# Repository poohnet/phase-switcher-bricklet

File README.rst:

Phase Switcher Bricklet
=======================

**This Bricklet is currently in development.**

This repository contains the firmware source code and the hardware design
files. The documentation generator configs can be found at
https://github.com/Tinkerforge/generators

Repository Content
------------------

software/:
 * examples/: Examples for all supported languages
 * build/: Compiled files
 * src/: Source code of firmware
 * Makefile: Makefile to build project

hardware/:
 * Contains KiCad project files and additionally schematics as PDF

datasheets/:
 * Contains datasheets for sensors and complex ICs that are used

Hardware
--------

The hardware is designed with the open source EDA Suite KiCad
(http://www.kicad.org). Before you are able to open the files,
you have to install the Tinkerforge kicad-libraries
(https://github.com/Tinkerforge/kicad-libraries). You can either clone
them directly in hardware/ or clone them in a separate folder and
symlink them into hardware/
(ln -s kicad_path/kicad-libraries project_path/hardware). After that you
can open the .pro file in hardware/ with KiCad and from there view and
modify the schematics and the PCB layout.

Software
--------

If you want to do your own Brick/Bricklet firmware development we highly
recommend that you use our build environment setup script and read the
tutorial (https://www.tinkerforge.com/en/doc/Tutorials/Tutorial_Build_Environment/Tutorial.html).

To compile the C code we recommend you to install the newest GNU Arm Embedded
Toolchain (https://launchpad.net/gcc-arm-embedded/+download).
You also need to install bricklib2 (https://github.com/Tinkerforge/bricklib2).

You can either clone it directly in software/src/ or clone it in a
separate folder and symlink it into software/src/
(ln -s bricklib_path/bricklib2 project_path/software/src/). Finally make sure to
have CMake installed (http://www.cmake.org/cmake/resources/software.html).

After that you can build the firmware by invoking make in software/.
The firmware (.zbin) can then be found in software/build/ and uploaded
with brickv (click button "Flashing" on start screen).

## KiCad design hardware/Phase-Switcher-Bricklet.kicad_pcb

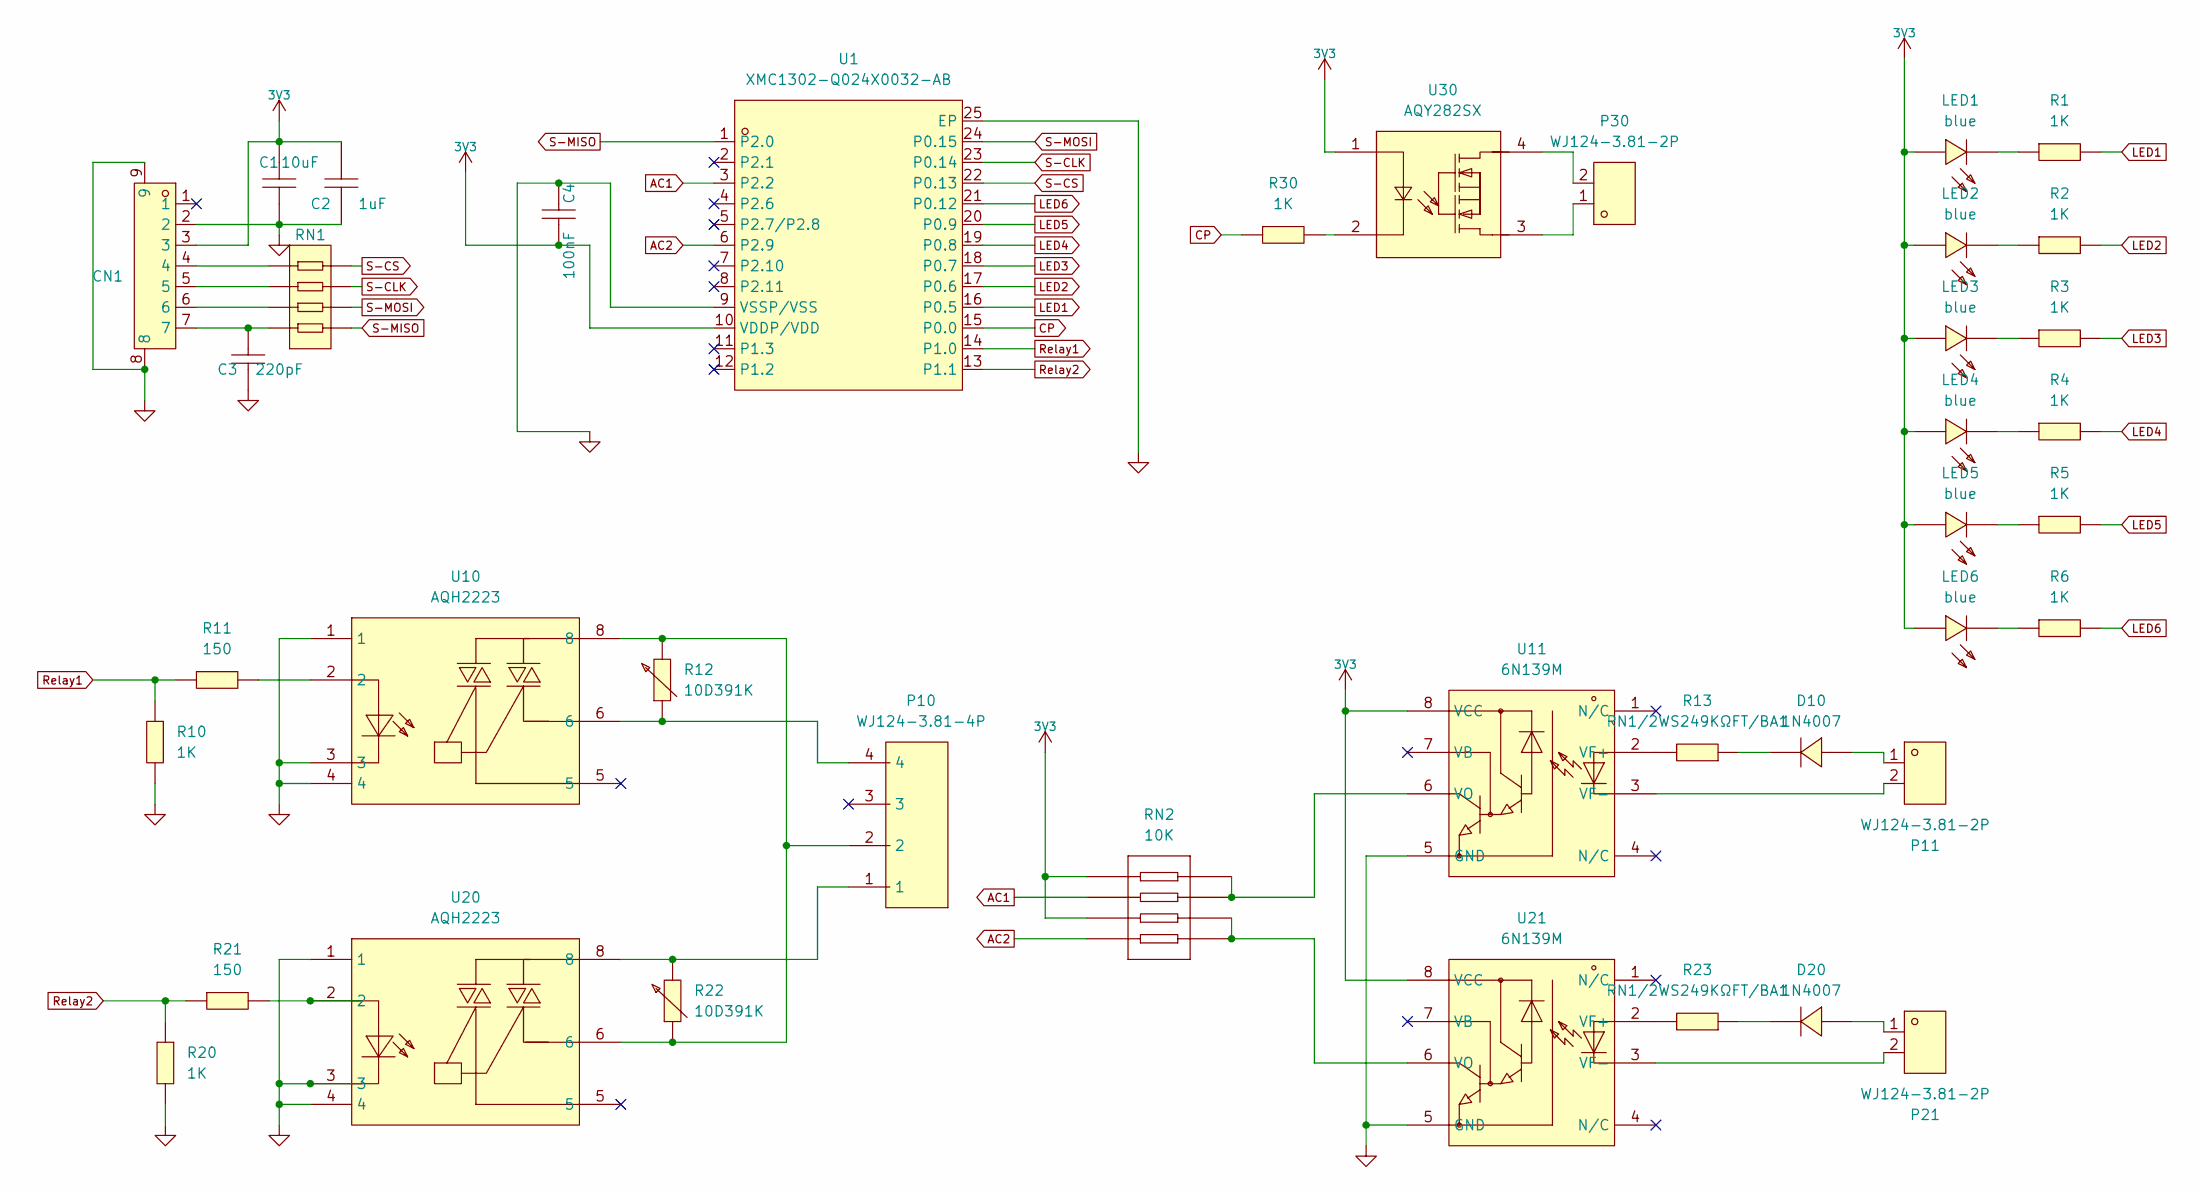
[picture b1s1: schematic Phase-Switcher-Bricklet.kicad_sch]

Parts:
C1: 10uF; C0805; LCSC Part C1222438
C2: 1uF; C0603; LCSC Part C513775
C3: 220pF; C0402; LCSC Part C107025
C4: 100nF; C0603; LCSC Part C30926
CN1: HC-GH-7PWTKK; CONN-SMD_7P-P1.25_HCTL_HC-GH-7PWTKK; LCSC Part C3011949
D10, D20: 1N4007; SOD-123FL_L2.8-W1.8-LS3.7-RD; LCSC Part C2902912
LED1, LED2, LED3, LED4, LED5, LED6: blue; LED0603-RD; LCSC Part C84266
P10: WJ124-3.81-4P; CONN-TH_4P-P3.81_KF124-3.81-4P; LCSC Part C69809
P11, P21, P30: WJ124-3.81-2P; CONN-TH_2P-P3.81_KF124-3.81-2P; LCSC Part C69811
R1, R2, R3, R4, R5, R6, R10, R20, R30: 1K; R0603; LCSC Part C22548
R11, R21: 150; R0603; LCSC Part C114608
R12, R22: 10D391K; RES-TH_L12.5-W6.2-P7.50-D0.9-S6.20; LCSC Part C139984
R13, R23: RN1/2WS249KΩFT/BA1; RES-TH_BD2.2-L6.5-P10.50-D0.6; LCSC Part C385480
RN1: CRA034RJ82RP05; RES-ARRAY-SMD_0603-8P-L3.2-W1.6-BL; LCSC Part C429276
RN2: 10K; RES-ARRAY-SMD_0603-8P-L3.2-W1.6-BL; LCSC Part C396839
U1: XMC1302-Q024X0032-AB; VQFN-24_L4.0-W4.0-P0.50-TL-EP2.7; LCSC Part C5121285
U10, U20: AQH2223; DIP-8_7P-L9.7-W6.4-P2.54-LS7.6-BL-PE7; LCSC Part C128520
U11, U21: 6N139M; DIP-8_L9.4-W6.4-P2.54-LS9.1-BL; LCSC Part C4071
U30: AQY282SX; SOP-4_L4.3-W4.4-P2.54-LS7.0-BL; LCSC Part C250827

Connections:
3V3: C1.1, C2.1, C4.2, CN1.3, LED1.2 (+), LED2.2 (+), LED3.2 (+), LED4.2 (+), LED5.2 (+), LED6.2 (+), RN2.5, RN2.7, U1.10 (VDDP/VDD), U11.8 (VCC), U21.8 (VCC), U30.1
AC1: RN2.6, U1.3 (P2.2)
AC2: RN2.8, U1.6 (P2.9)
CP: R30.1, U1.15 (P0.0)
GND: C1.2, C2.2, C3.2, C4.1, CN1.2, CN1.8, CN1.9, R10.2, R20.2, U1.9 (VSSP/VSS), U1.25 (EP), U10.1, U10.3, U10.4, U11.5 (GND), U20.1, U20.3, U20.4, U21.5 (GND)
LED1: R1.2, U1.16 (P0.5)
LED2: R2.2, U1.17 (P0.6)
LED3: R3.2, U1.18 (P0.7)
LED4: R4.2, U1.19 (P0.8)
LED5: R5.2, U1.20 (P0.9)
LED6: R6.2, U1.21 (P0.12)
unnamed: C3.1, CN1.7, RN1.4
unnamed: CN1.4, RN1.1
unnamed: CN1.5, RN1.2
unnamed: CN1.6, RN1.3
unnamed: D10.2 (A), P11.1
unnamed: D10.1 (K), R13.1
unnamed: D20.2 (A), P21.1
unnamed: D20.1 (K), R23.1
unnamed: LED1.1 (-), R1.1
unnamed: LED2.1 (-), R2.1
unnamed: LED3.1 (-), R3.1
unnamed: LED4.1 (-), R4.1
unnamed: LED5.1 (-), R5.1
unnamed: LED6.1 (-), R6.1
unnamed: P10.1, R22.2, U20.8
unnamed: P10.2, R12.2, R22.1, U10.8, U20.6
unnamed: P10.4, R12.1, U10.6
unnamed: P30.1, U30.3
unnamed: P30.2, U30.4
unnamed: R11.2, U10.2
unnamed: R21.2, U20.2
unnamed: R30.2, U30.2
unnamed: R13.2, U11.2 (VF+)
unnamed: P11.2, U11.3 (VF-)
unnamed: RN2.3, RN2.4, U11.6 (VO)
unnamed: R23.2, U21.2 (VF+)
unnamed: P21.2, U21.3 (VF-)
unnamed: RN2.1, RN2.2, U21.6 (VO)
Relay1: R10.1, R11.1, U1.14 (P1.0)
Relay2: R20.1, R21.1, U1.13 (P1.1)
S-CLK: RN1.7, U1.23 (P0.14)
S-CS: RN1.8, U1.22 (P0.13)
S-MISO: RN1.5, U1.1 (P2.0)
S-MOSI: RN1.6, U1.24 (P0.15)

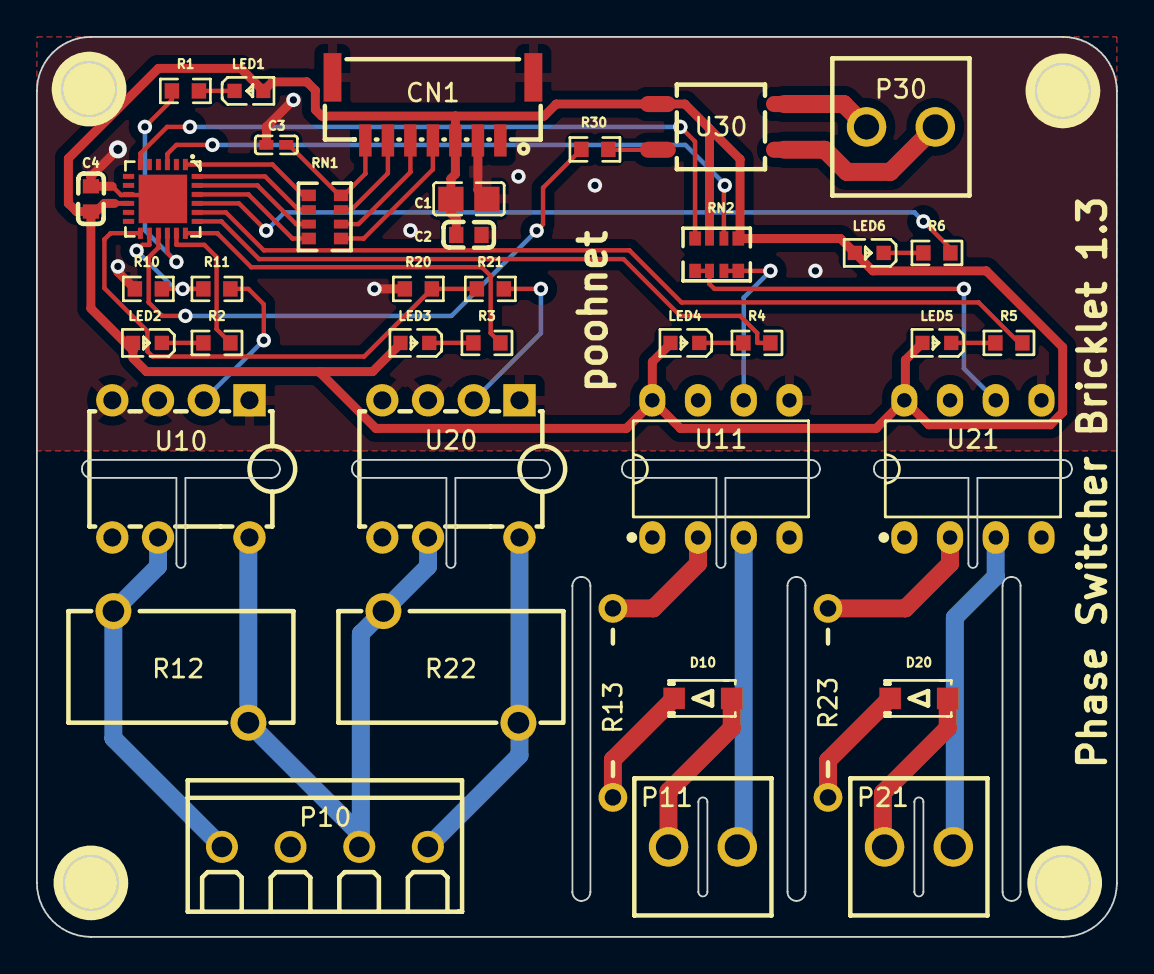
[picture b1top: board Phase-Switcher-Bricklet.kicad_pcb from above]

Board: 2 copper layers, 60.0 x 50.0 mm, 40 parts (0 on the bottom side), 45 nets.

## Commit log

2024-02-06 Add KiCad files and datasheets
2024-02-18 Phase-Switcher-Bricklet: Rev. 1.1
2024-02-21 Phase-Switcher-Bricklet: Rev. 1.1a
2024-02-22 Phase-Switcher-Bricklet: Rev. 1.2
2024-02-24 Phase-Switcher-Bricklet: Rev. 1.3
2024-02-24 Add firmware stub
2024-03-01 Add ac_in, ac_relay and dc_relay
2024-03-06 Add logic
